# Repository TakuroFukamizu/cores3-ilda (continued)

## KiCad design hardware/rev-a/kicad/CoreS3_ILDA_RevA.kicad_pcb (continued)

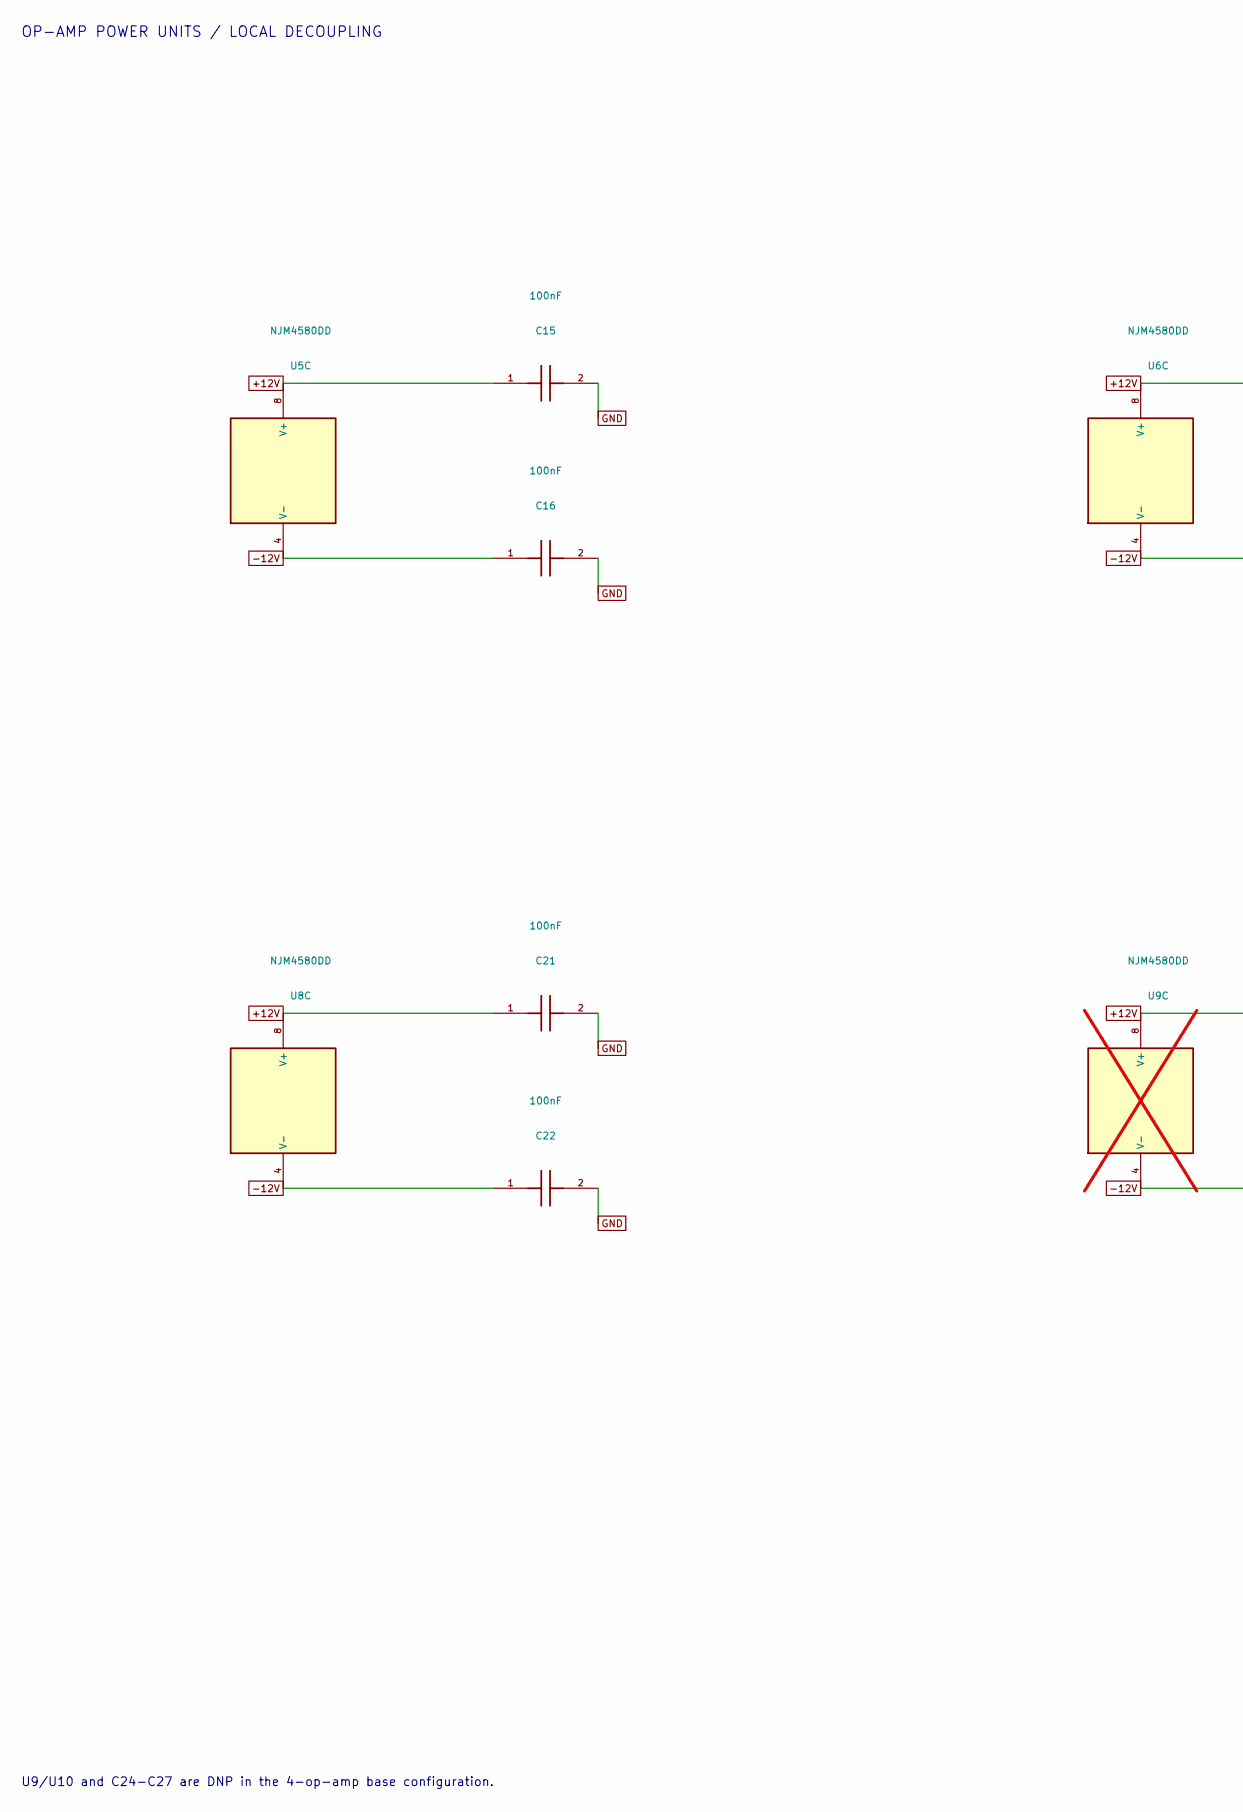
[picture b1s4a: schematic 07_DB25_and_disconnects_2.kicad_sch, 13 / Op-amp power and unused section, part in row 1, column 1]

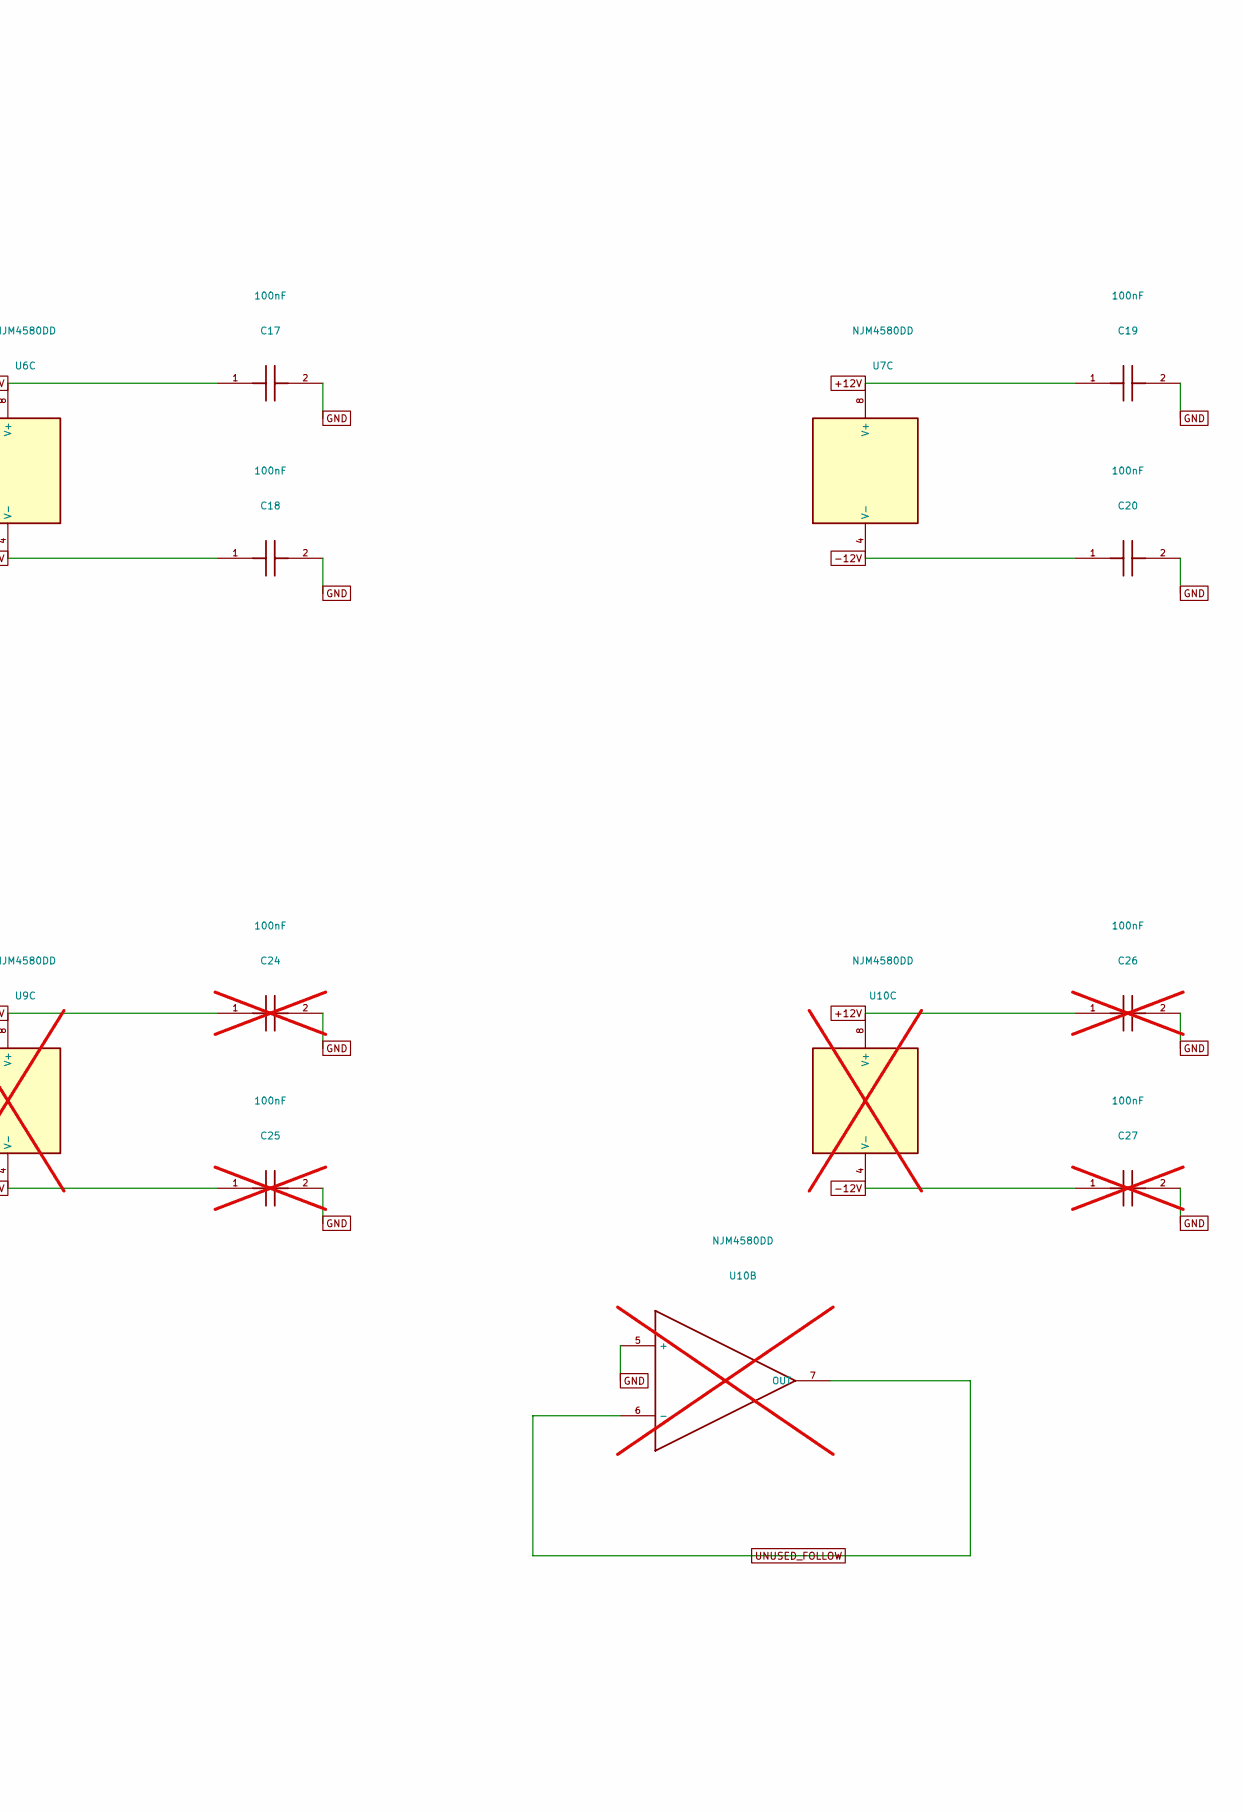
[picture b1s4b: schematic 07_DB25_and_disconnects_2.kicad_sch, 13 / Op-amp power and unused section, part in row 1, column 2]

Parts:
C15, C16, C17, C18, C19, C20, C21, C22: 100nF; C_Disc_D5.0mm_W2.5mm_P5.00mm
C24, C25, C26, C27: 100nF; C_Disc_D5.0mm_W2.5mm_P5.00mm; not fitted
U5, U6, U7, U8: NJM4580DD; DIP-8_W7.62mm
U9, U10: NJM4580DD; DIP-8_W7.62mm; not fitted

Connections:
+12V: C15.1, C17.1, C19.1, C21.1, C24.1, C26.1, U5.8 (V+), U6.8 (V+), U7.8 (V+), U8.8 (V+), U9.8 (V+), U10.8 (V+); also elsewhere on the board
-12V: C16.1, C18.1, C20.1, C22.1, C25.1, C27.1, U5.4 (V-), U6.4 (V-), U7.4 (V-), U8.4 (V-), U9.4 (V-), U10.4 (V-); also elsewhere on the board
GND: C15.2, C16.2, C17.2, C18.2, C19.2, C20.2, C21.2, C22.2, C24.2, C25.2, C26.2, C27.2, U10.5 (+); also elsewhere on the board
UNUSED_FOLLOW: U10.6 (-), U10.7 (OUT)

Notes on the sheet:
OP-AMP POWER UNITS / LOCAL DECOUPLING
U9/U10 and C24-C27 are DNP in the 4-op-amp base configuration.

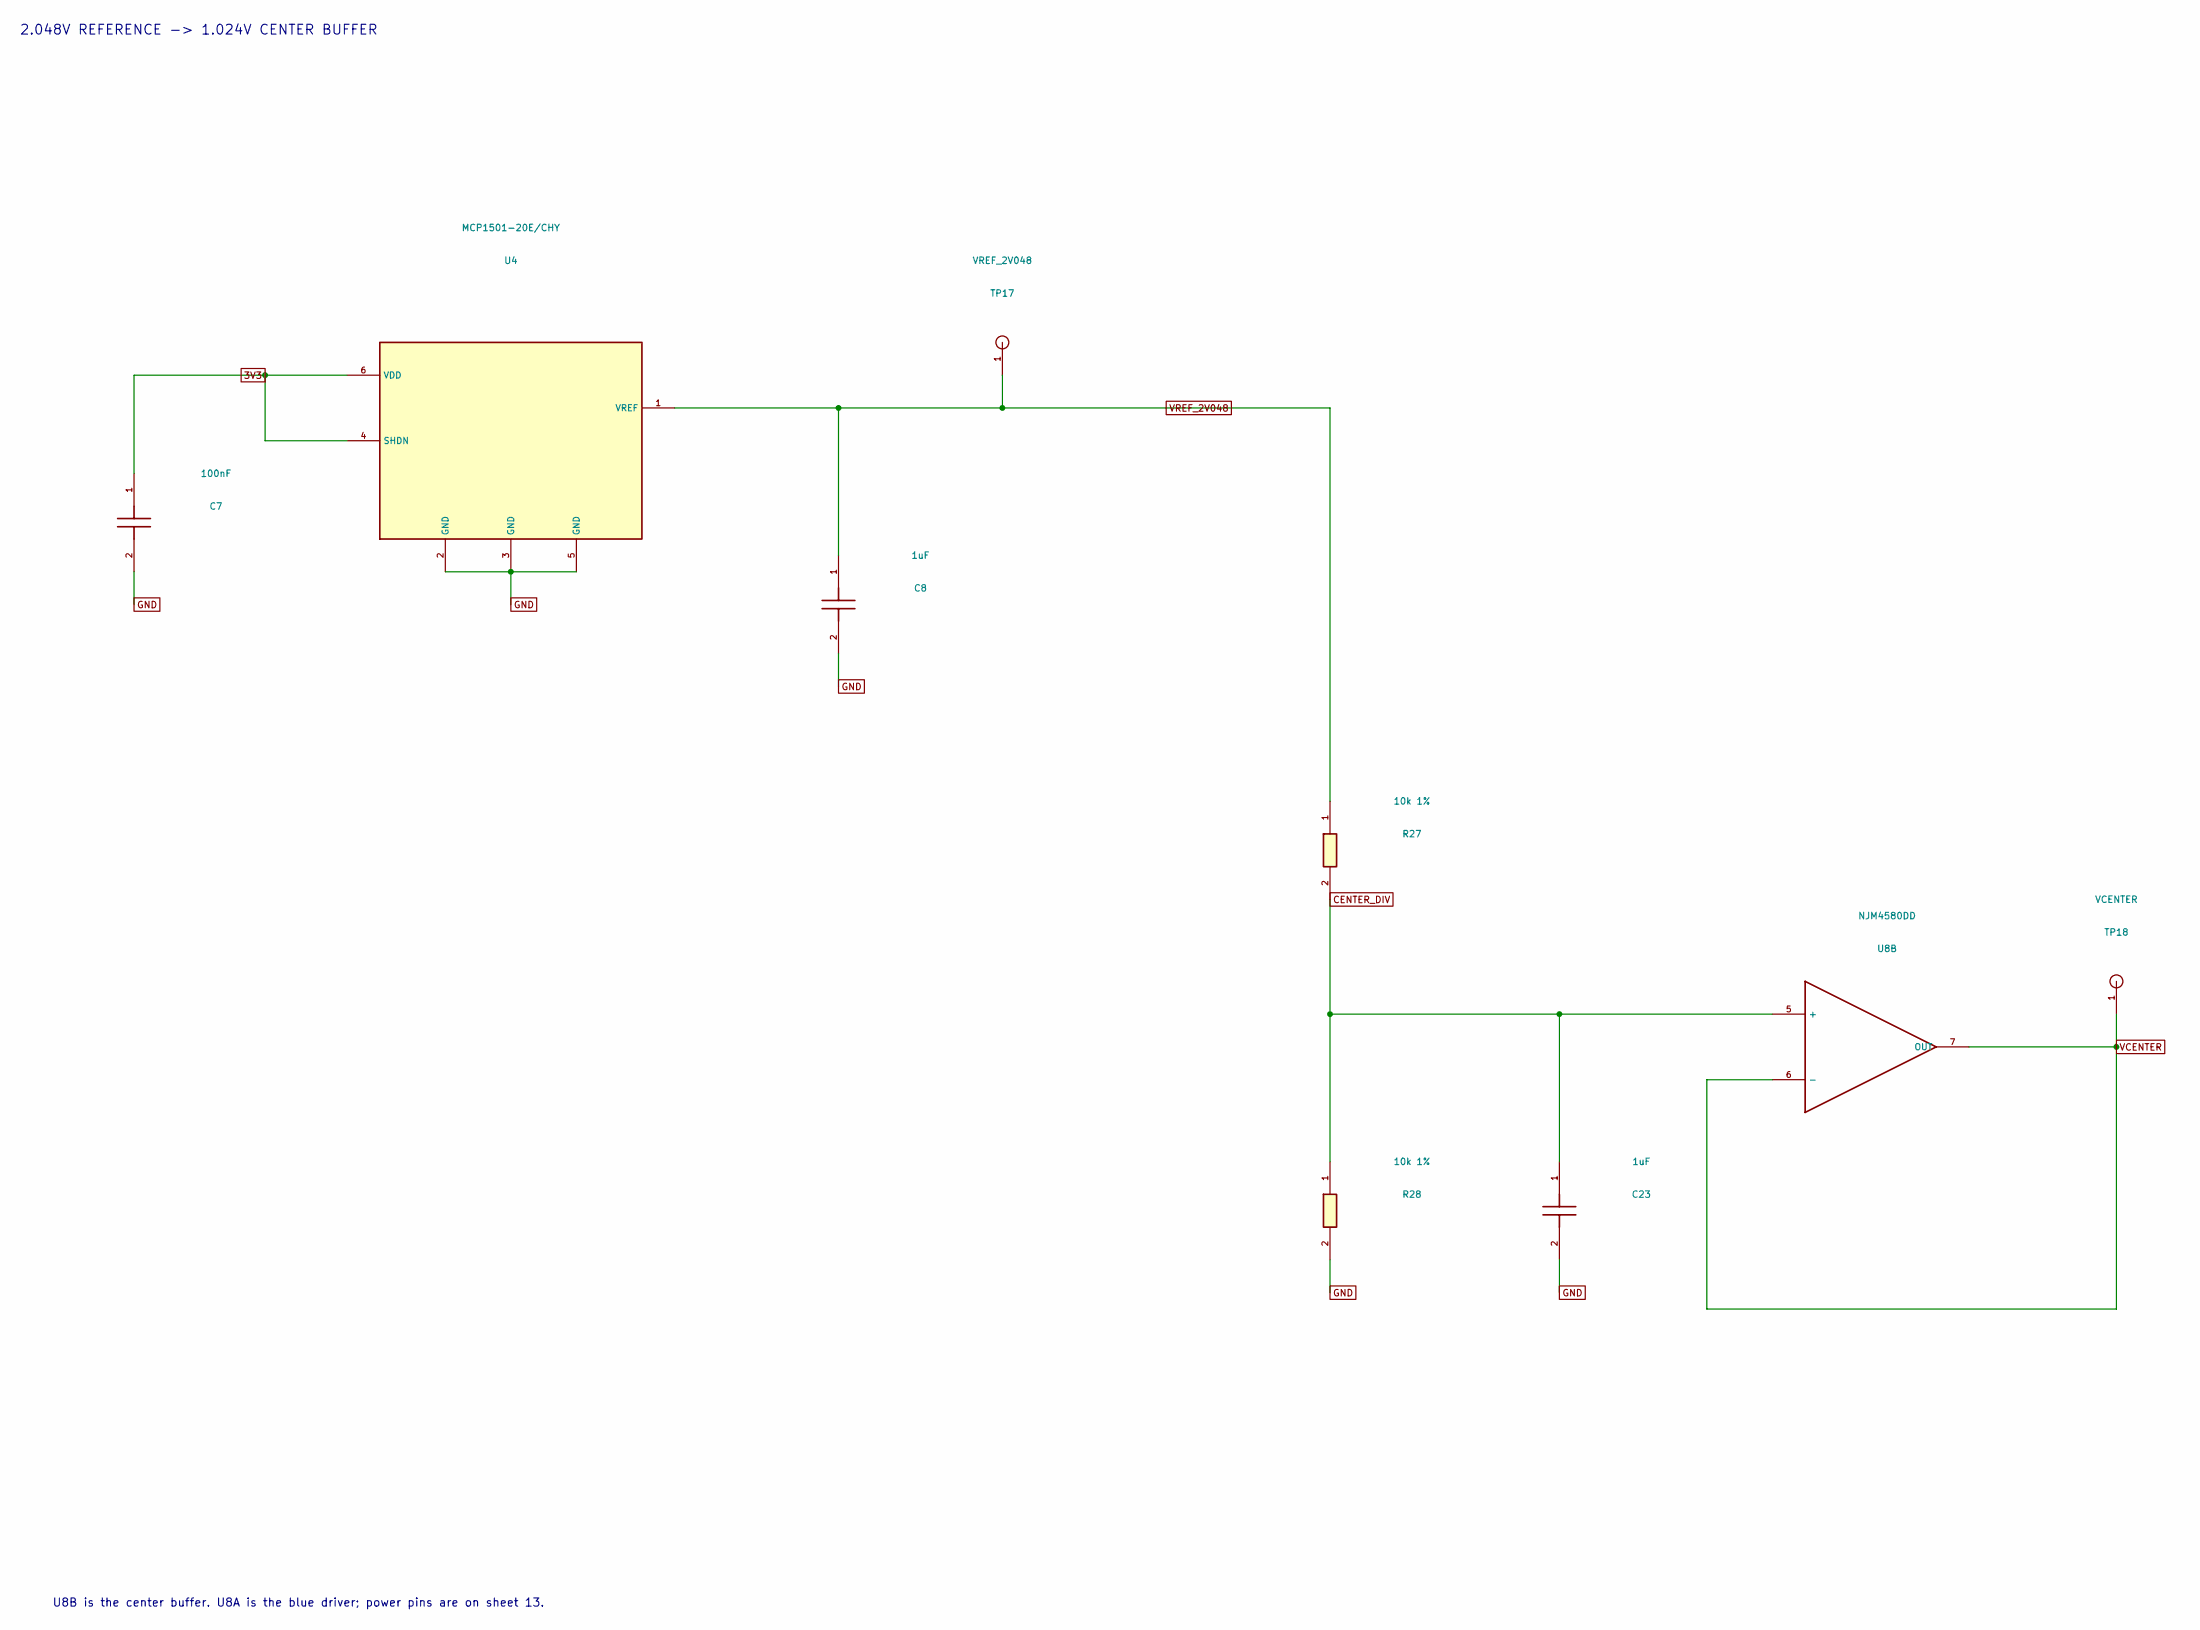
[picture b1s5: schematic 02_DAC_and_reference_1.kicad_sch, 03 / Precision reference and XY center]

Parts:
C7: 100nF; C_Disc_D5.0mm_W2.5mm_P5.00mm
C8, C23: 1uF; C_Disc_D5.0mm_W2.5mm_P5.00mm
R27, R28: 10k 1%; R_Axial_DIN0207_L6.3mm_D2.5mm_P10.16mm_Horizontal
TP17: VREF_2V048; TestPoint_THTPad_D2.0mm_Drill1.0mm
TP18: VCENTER; TestPoint_THTPad_D2.0mm_Drill1.0mm
U4: MCP1501-20E/CHY; SOT-23-6
U8: NJM4580DD; DIP-8_W7.62mm

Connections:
3V3: C7.1, U4.4 (SHDN), U4.6 (VDD); also elsewhere on the board
CENTER_DIV: C23.1, R27.2, R28.1, U8.5 (+)
GND: C7.2, C8.2, C23.2, R28.2, U4.2 (GND), U4.3 (GND), U4.5 (GND); also elsewhere on the board
VCENTER: TP18.1, U8.6 (-), U8.7 (OUT); also elsewhere on the board
VREF_2V048: C8.1, R27.1, TP17.1, U4.1 (VREF); also elsewhere on the board

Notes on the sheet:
2.048V REFERENCE -> 1.024V CENTER BUFFER
U8B is the center buffer. U8A is the blue driver; power pins are on sheet 13.

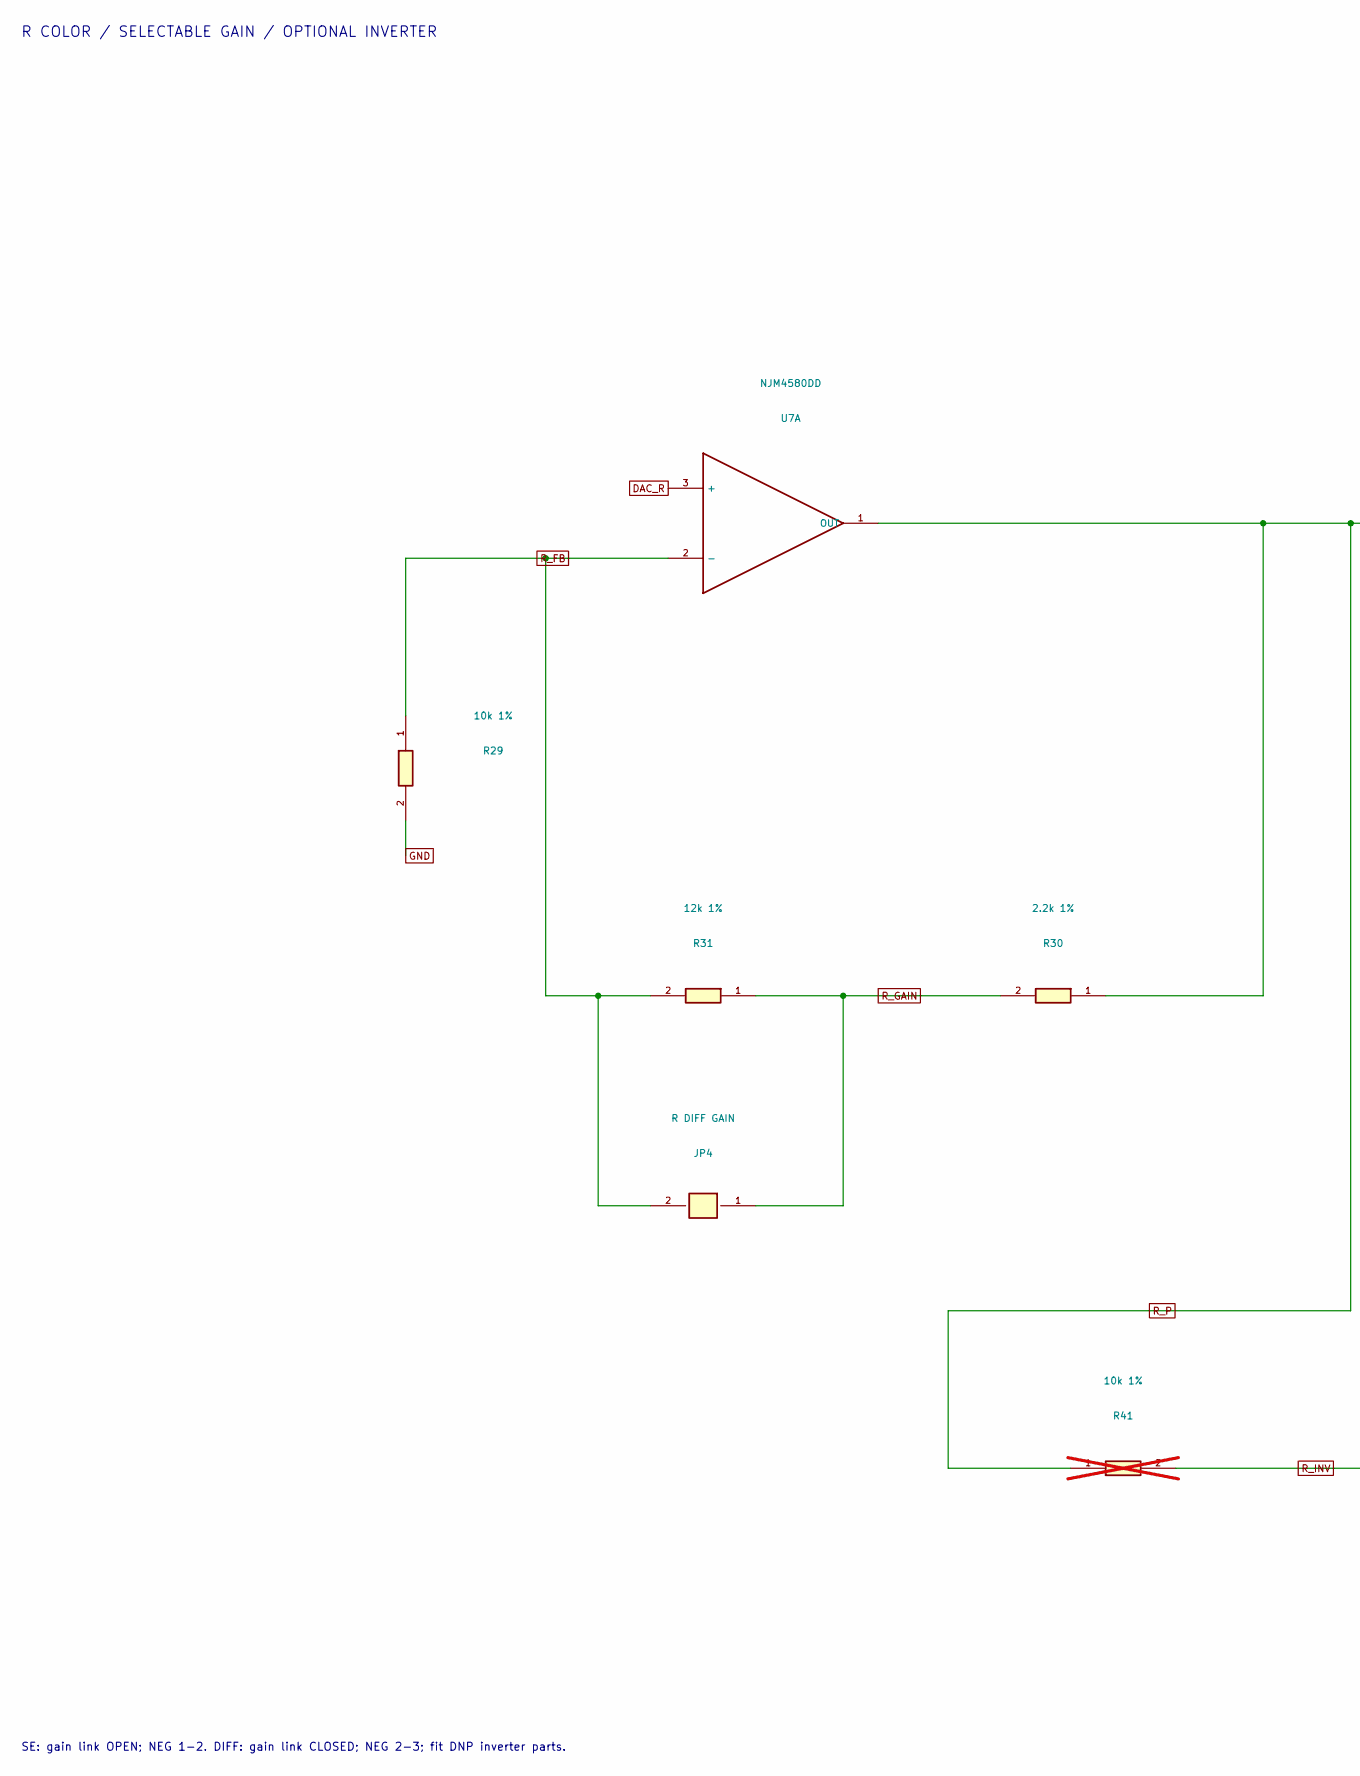
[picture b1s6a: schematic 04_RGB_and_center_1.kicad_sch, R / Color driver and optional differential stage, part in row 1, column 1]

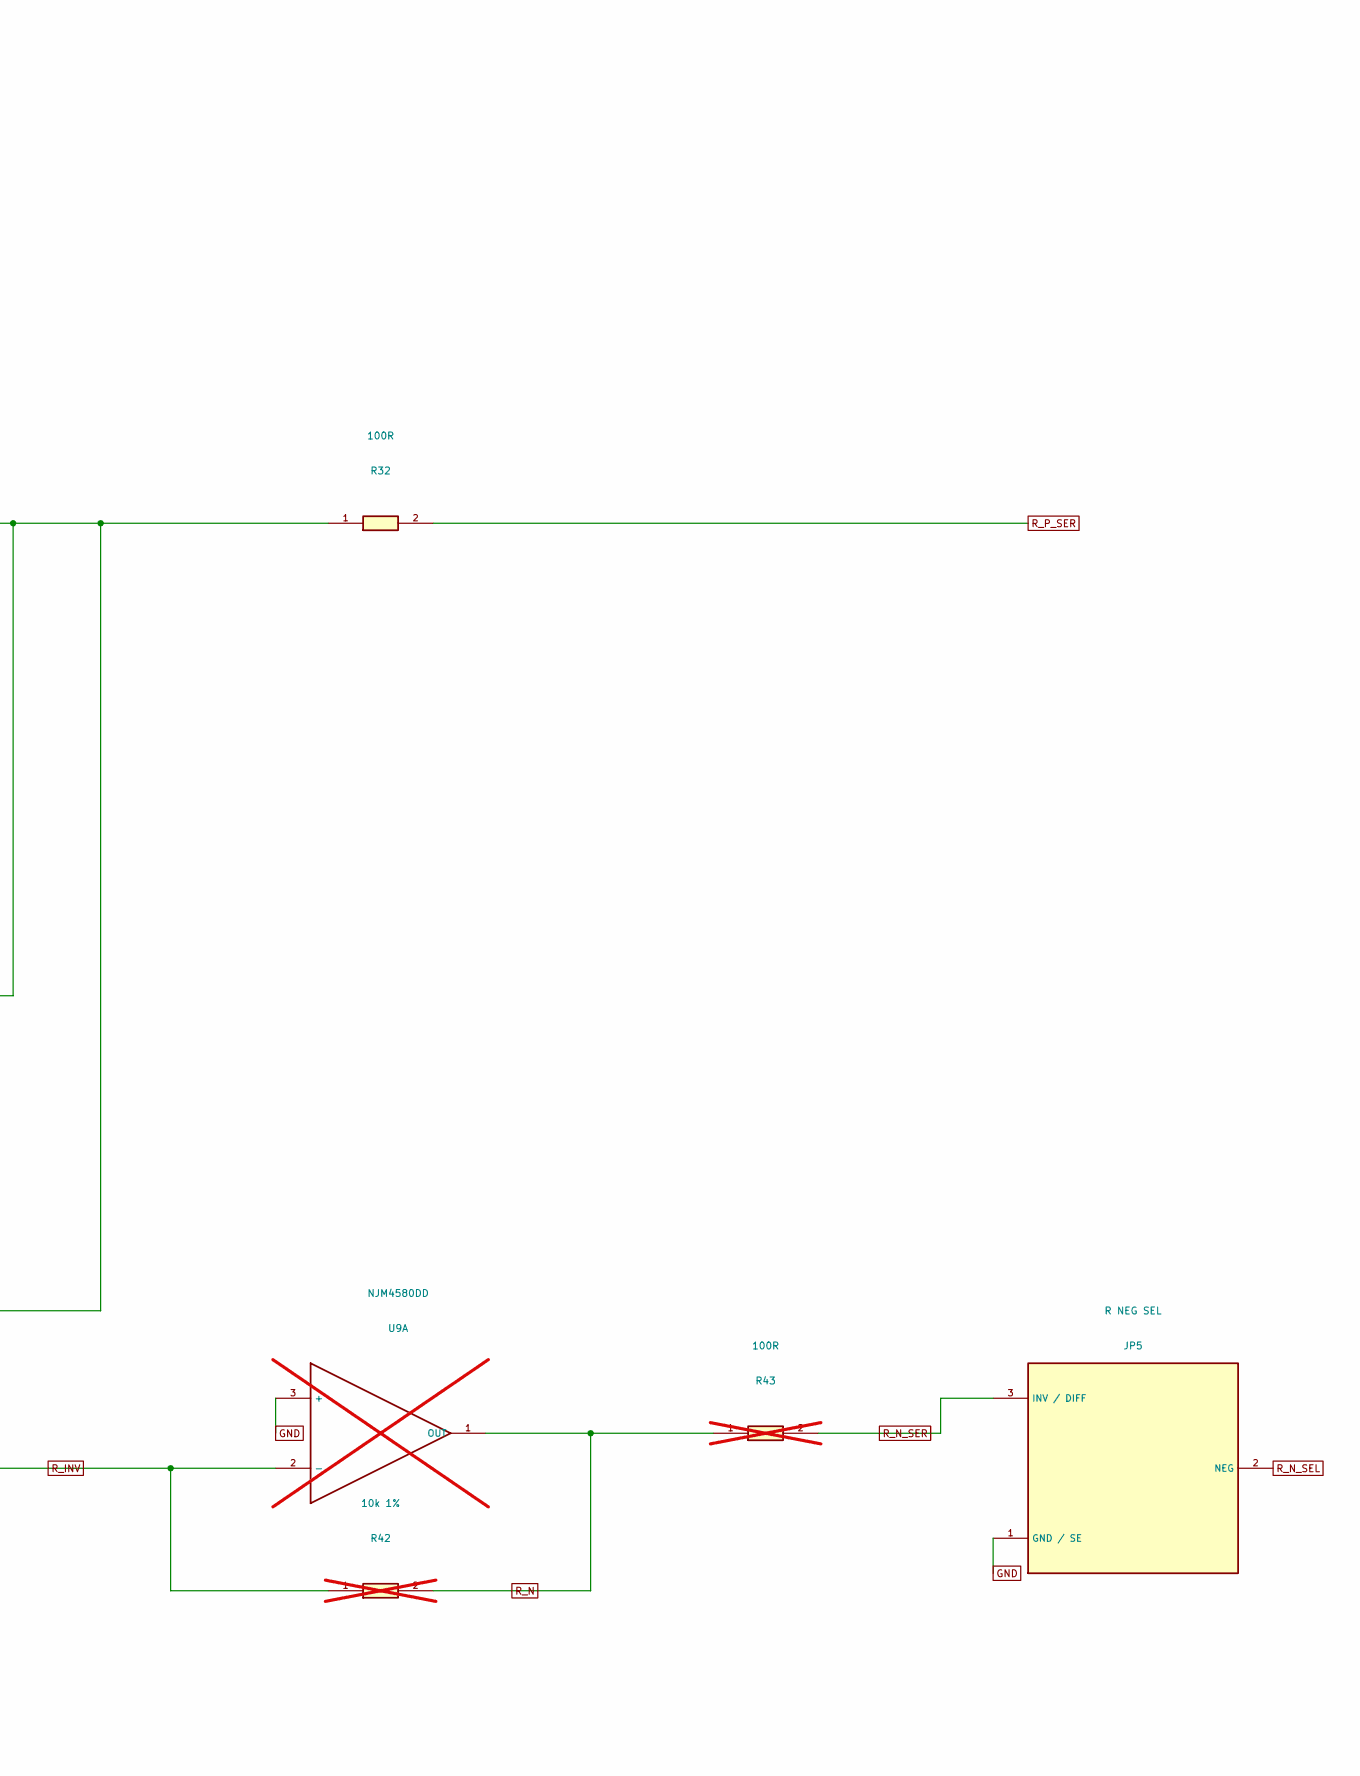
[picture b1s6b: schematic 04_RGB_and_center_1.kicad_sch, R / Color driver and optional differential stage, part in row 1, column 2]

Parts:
JP4: R DIFF GAIN; PinHeader_1x02_P2.54mm_Vertical
JP5: R NEG SEL; PinHeader_1x03_P2.54mm_Vertical
R29: 10k 1%; R_Axial_DIN0207_L6.3mm_D2.5mm_P10.16mm_Horizontal
R30: 2.2k 1%; R_Axial_DIN0207_L6.3mm_D2.5mm_P10.16mm_Horizontal
R31: 12k 1%; R_Axial_DIN0207_L6.3mm_D2.5mm_P10.16mm_Horizontal
R32: 100R; R_Axial_DIN0207_L6.3mm_D2.5mm_P10.16mm_Horizontal
R41, R42: 10k 1%; R_Axial_DIN0207_L6.3mm_D2.5mm_P10.16mm_Horizontal; not fitted
R43: 100R; R_Axial_DIN0207_L6.3mm_D2.5mm_P10.16mm_Horizontal; not fitted
U7: NJM4580DD; DIP-8_W7.62mm
U9: NJM4580DD; DIP-8_W7.62mm; not fitted

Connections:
DAC_R: U7.3 (+); also elsewhere on the board
GND: JP5.1 (GND / SE), R29.2, U9.3 (+); also elsewhere on the board
R_FB: JP4.2, R29.1, R31.2, U7.2 (-)
R_GAIN: JP4.1, R30.2, R31.1
R_INV: R41.2, R42.1, U9.2 (-)
R_N: R42.2, R43.1, U9.1 (OUT)
R_N_SEL: JP5.2 (NEG); also elsewhere on the board
R_N_SER: JP5.3 (INV / DIFF), R43.2
R_P: R30.1, R32.1, R41.1, U7.1 (OUT)
R_P_SER: R32.2; also elsewhere on the board

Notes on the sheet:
R COLOR / SELECTABLE GAIN / OPTIONAL INVERTER
SE: gain link OPEN; NEG 1-2. DIFF: gain link CLOSED; NEG 2-3; fit DNP inverter parts.

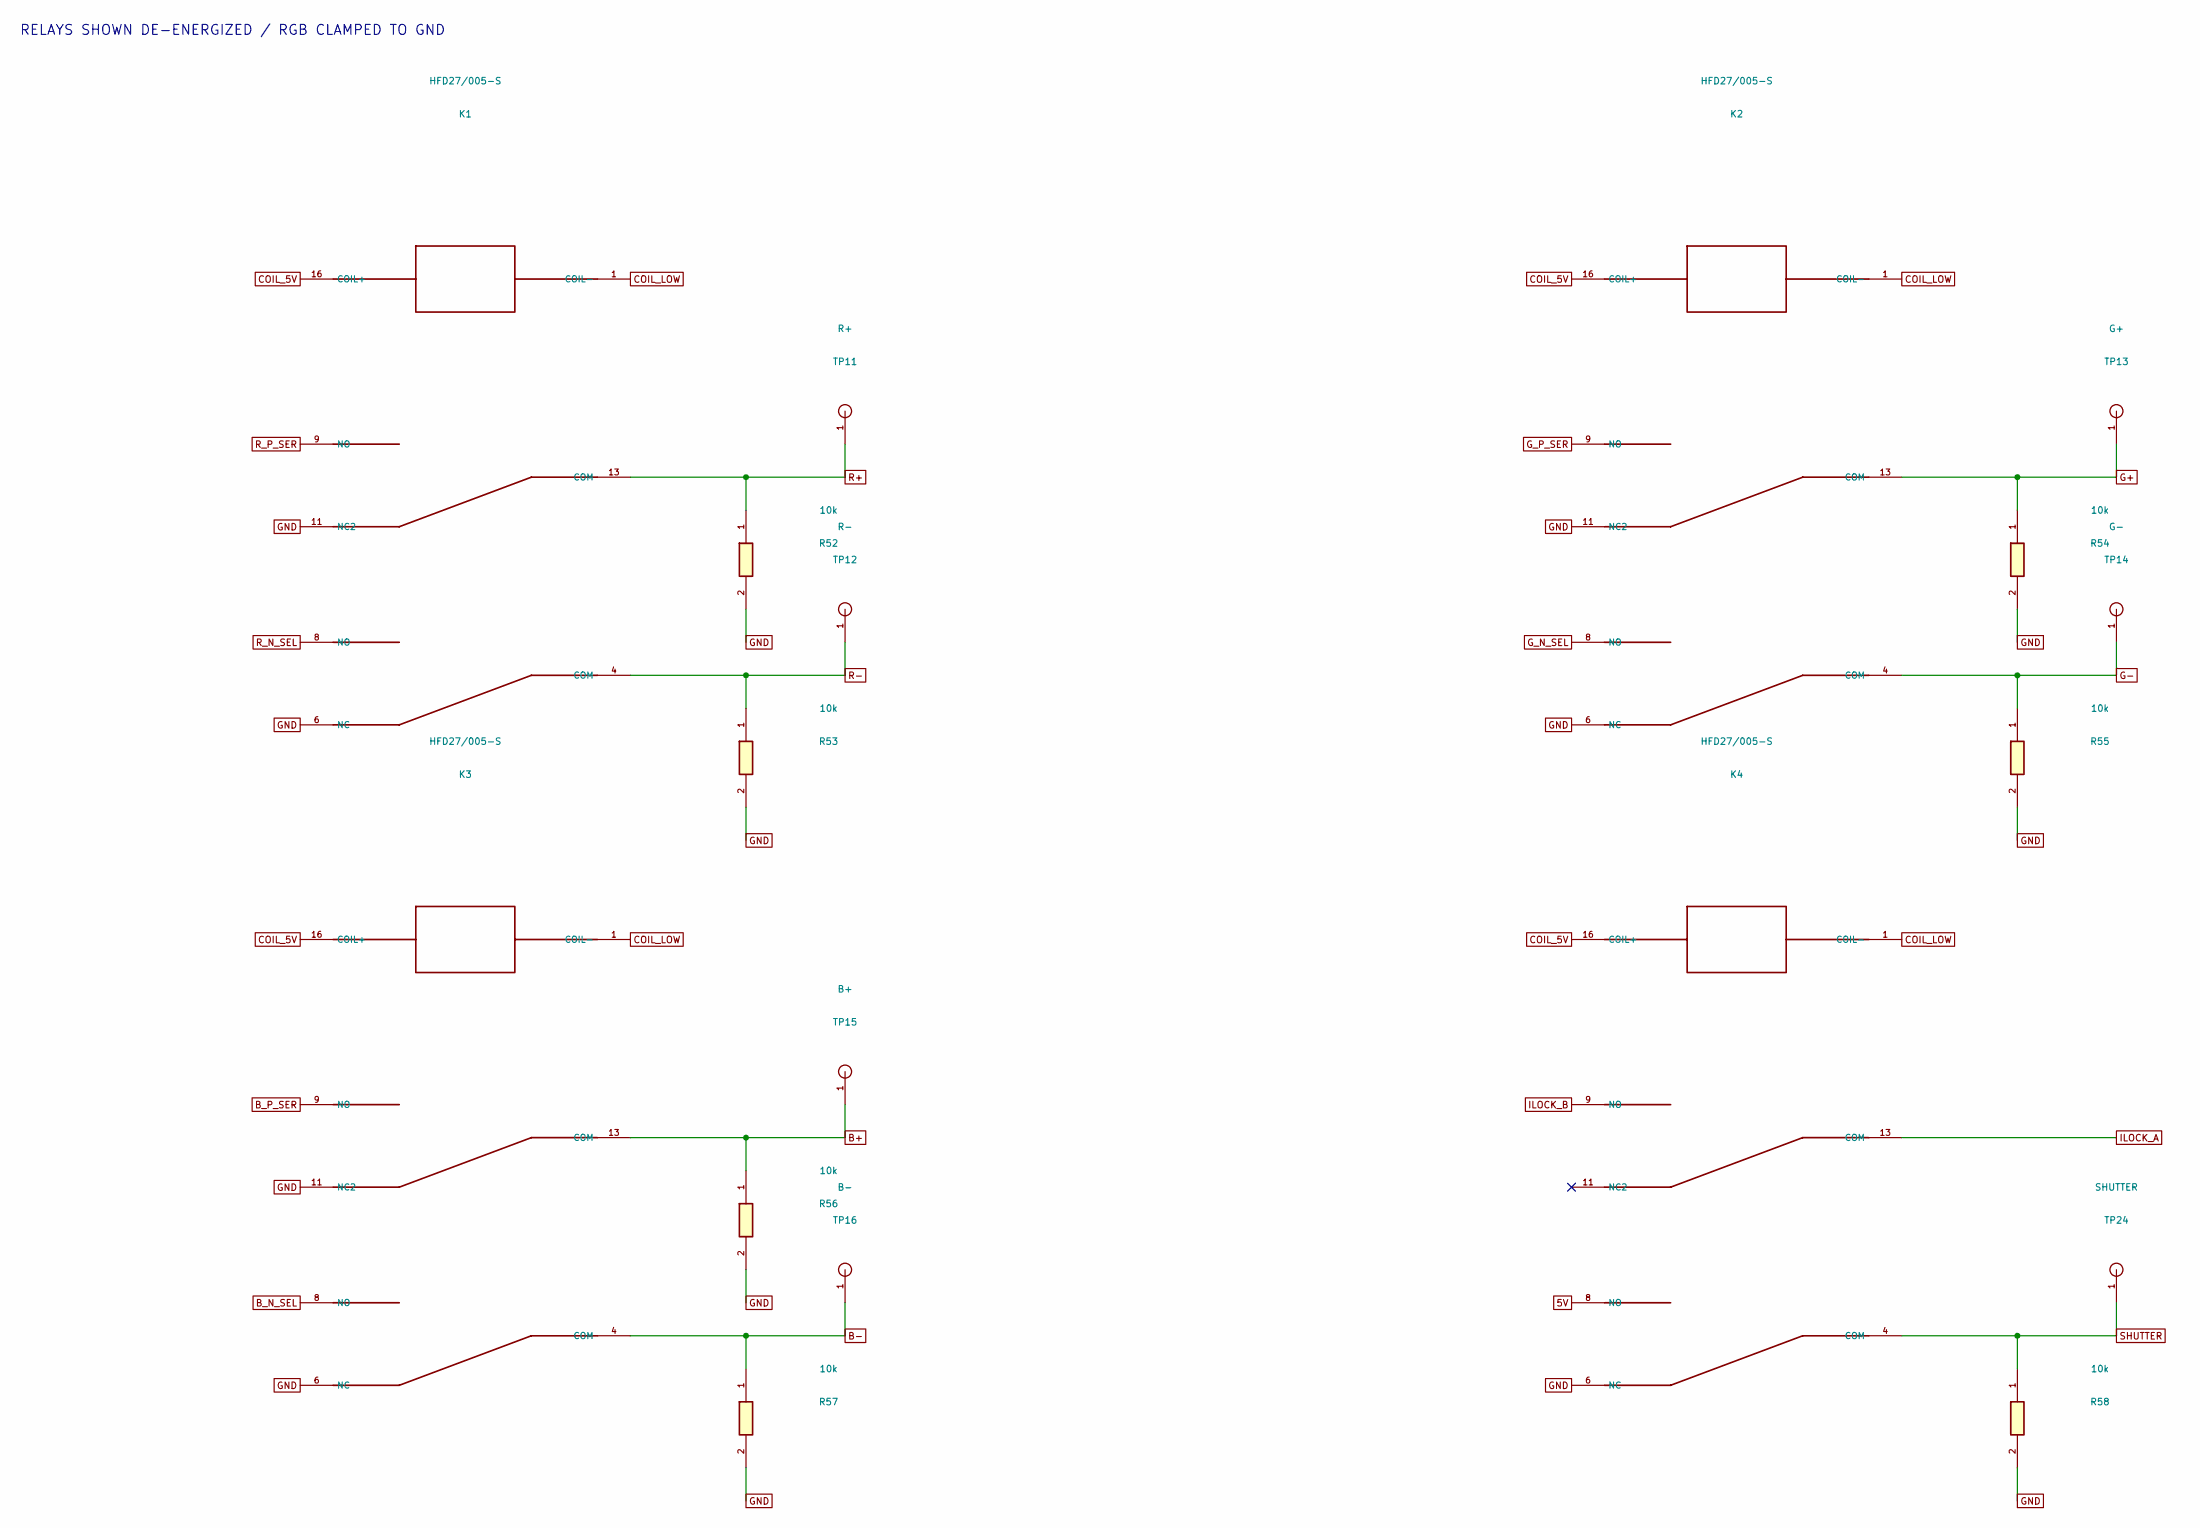
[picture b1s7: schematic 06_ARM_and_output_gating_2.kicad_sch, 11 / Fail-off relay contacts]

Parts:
K1, K2, K3, K4: HFD27/005-S; HFD27
R52, R53, R54, R55, R56, R57, R58: 10k; R_Axial_DIN0207_L6.3mm_D2.5mm_P10.16mm_Horizontal
TP11: R+; TestPoint_THTPad_D2.0mm_Drill1.0mm
TP12: R-; TestPoint_THTPad_D2.0mm_Drill1.0mm
TP13: G+; TestPoint_THTPad_D2.0mm_Drill1.0mm
TP14: G-; TestPoint_THTPad_D2.0mm_Drill1.0mm
TP15: B+; TestPoint_THTPad_D2.0mm_Drill1.0mm
TP16: B-; TestPoint_THTPad_D2.0mm_Drill1.0mm
TP24: SHUTTER; TestPoint_THTPad_D2.0mm_Drill1.0mm

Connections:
5V: K4.8 (NO); also elsewhere on the board
B+: K3.13 (COM), R56.1, TP15.1; also elsewhere on the board
B-: K3.4 (COM), R57.1, TP16.1; also elsewhere on the board
B_N_SEL: K3.8 (NO); also elsewhere on the board
B_P_SER: K3.9 (NO); also elsewhere on the board
COIL_5V: K1.16 (COIL+), K2.16 (COIL+), K3.16 (COIL+), K4.16 (COIL+); also elsewhere on the board
COIL_LOW: K1.1 (COIL-), K2.1 (COIL-), K3.1 (COIL-), K4.1 (COIL-); also elsewhere on the board
G+: K2.13 (COM), R54.1, TP13.1; also elsewhere on the board
G-: K2.4 (COM), R55.1, TP14.1; also elsewhere on the board
GND: K1.6 (NC), K1.11 (NC2), K2.6 (NC), K2.11 (NC2), K3.6 (NC), K3.11 (NC2), K4.6 (NC), R52.2, R53.2, R54.2, R55.2, R56.2, R57.2, R58.2; also elsewhere on the board
G_N_SEL: K2.8 (NO); also elsewhere on the board
G_P_SER: K2.9 (NO); also elsewhere on the board
ILOCK_A: K4.13 (COM); also elsewhere on the board
ILOCK_B: K4.9 (NO); also elsewhere on the board
R+: K1.13 (COM), R52.1, TP11.1; also elsewhere on the board
R-: K1.4 (COM), R53.1, TP12.1; also elsewhere on the board
R_N_SEL: K1.8 (NO); also elsewhere on the board
R_P_SER: K1.9 (NO); also elsewhere on the board
SHUTTER: K4.4 (COM), R58.1, TP24.1; also elsewhere on the board

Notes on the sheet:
RELAYS SHOWN DE-ENERGIZED / RGB CLAMPED TO GND
